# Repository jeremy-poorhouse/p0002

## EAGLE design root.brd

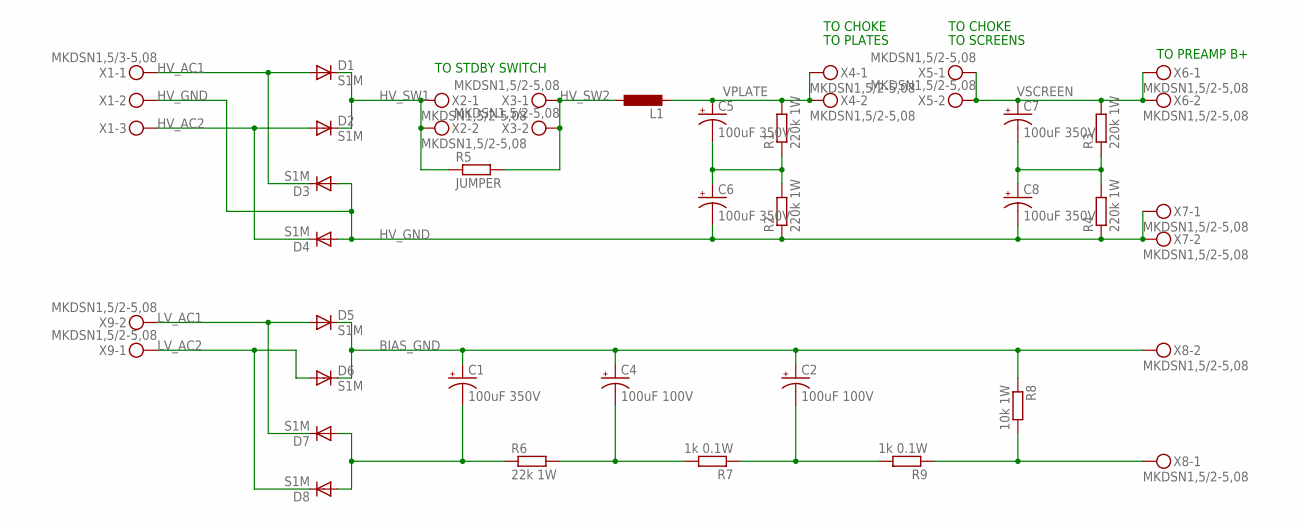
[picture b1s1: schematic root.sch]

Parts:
C1, C5, C6, C7, C8: 100uF 350V; E7,5-18
C2, C4: 100uF 100V; PANASONIC_F
D1, D2, D3, D4, D5, D6, D7, D8: S1M; SMA
L1: L-EUL4516C; L4516C
R1, R2, R3, R4: 220k 1W; R2512
R5: JUMPER; R1206
R6: 22k 1W; R2512
R7, R9: 1k 0.1W; R0603
R8: 10k 1W; R2512
X1: MKDSN1,5/3-5,08
X2, X3, X4, X5, X6, X7, X8, X9: MKDSN1,5/2-5,08

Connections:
BIAS_GND: C1.+, C2.+, C4.+, D5.C, D6.C, R8.1, X8.2
HV_AC1: D1.A, D3.C, X1.1
HV_AC2: D2.A, D4.C, X1.3
HV_GND: C6.-, C8.-, D3.A, D4.A, R2.1, R4.1, X1.2, X7.1, X7.2
HV_SW1: D1.C, D2.C, R5.1, X2.1, X2.2
HV_SW2: L1.1, R5.2, X3.1, X3.2
LV_AC1: D5.A, D7.C, X9.2
LV_AC2: D6.A, D8.C, X9.1
unnamed: C5.-, C6.+, R1.1, R2.2
unnamed: R8.2, R9.1, X8.1
unnamed: C4.-, R6.2, R7.2
unnamed: C7.-, C8.+, R3.1, R4.2
unnamed: C2.-, R7.1, R9.2
unnamed: C1.-, D7.A, D8.A, R6.1
VPLATE: C5.+, L1.2, R1.2, X4.1, X4.2
VSCREEN: C7.+, R3.2, X5.1, X5.2, X6.1, X6.2

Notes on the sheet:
TO STDBY SWITCH
TO PLATES
TO CHOKE
TO SCREENS
TO PREAMP B+

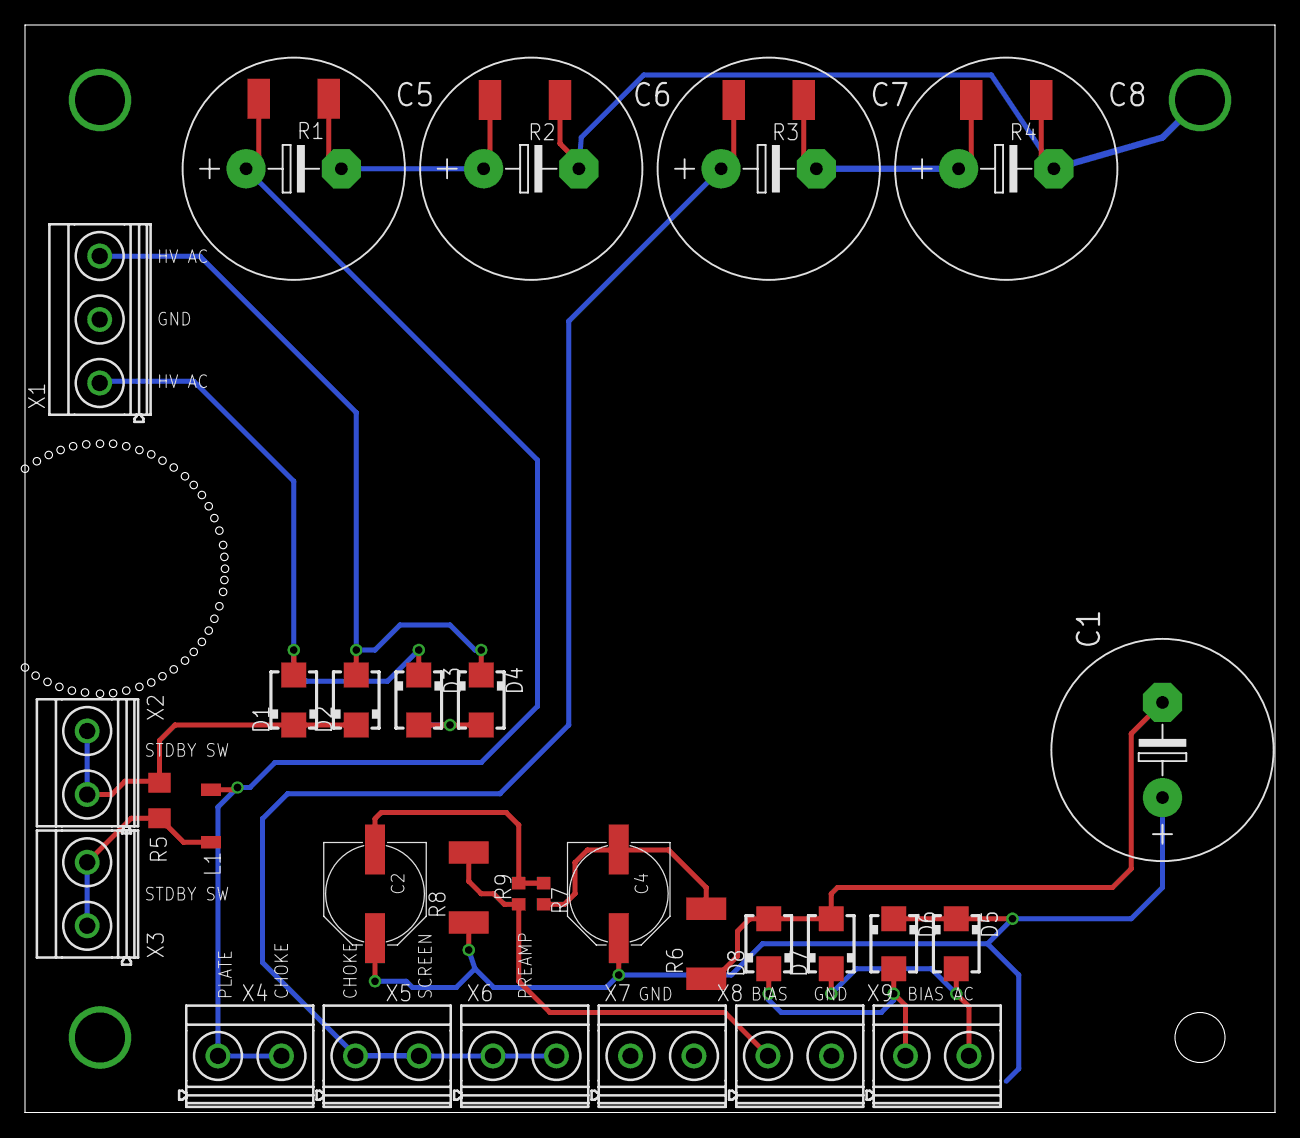
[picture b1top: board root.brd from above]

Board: 2 copper layers, 100.0 x 87.0 mm, 34 parts (0 on the bottom side), 16 nets.

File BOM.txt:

Partlist exported from /Users/jeremyhale/Documents/eagle/poorhouseamps/power_supply/root.sch at 2015-03-23 2:21 PM

Part Value           Device          Package         Description                          
C1   100uF 350V      CPOL-USE7.5-18  E7,5-18         POLARIZED CAPACITOR, American symbol 
C2   100uF 100V      CPOL-USF        PANASONIC_F     POLARIZED CAPACITOR, American symbol 
C4   100uF 100V      CPOL-USF        PANASONIC_F     POLARIZED CAPACITOR, American symbol 
C5   100uF 350V      CPOL-USE7.5-18  E7,5-18         POLARIZED CAPACITOR, American symbol 
C6   100uF 350V      CPOL-USE7.5-18  E7,5-18         POLARIZED CAPACITOR, American symbol 
C7   100uF 350V      CPOL-USE7.5-18  E7,5-18         POLARIZED CAPACITOR, American symbol 
C8   100uF 350V      CPOL-USE7.5-18  E7,5-18         POLARIZED CAPACITOR, American symbol 
D1   S1M             S1M             SMA                                                  
D2   S1M             S1M             SMA                                                  
D3   S1M             S1M             SMA                                                  
D4   S1M             S1M             SMA                                                  
D5   S1M             S1M             SMA                                                  
D6   S1M             S1M             SMA                                                  
D7   S1M             S1M             SMA                                                  
D8   S1M             S1M             SMA                                                  
L1                   L-EUL4516C      L4516C          INDUCTOR, European symbol            
R1   220k 1W         R-EU_R2512      R2512           RESISTOR, European symbol            
R2   220k 1W         R-EU_R2512      R2512           RESISTOR, European symbol            
R3   220k 1W         R-EU_R2512      R2512           RESISTOR, European symbol            
R4   220k 1W         R-EU_R2512      R2512           RESISTOR, European symbol            
R5   JUMPER          R-EU_R1206      R1206           RESISTOR, European symbol            
R6   22k 1W          R-EU_R2512      R2512           RESISTOR, European symbol            
R7   1k 1W           R-EU_R0603      R0603           RESISTOR, European symbol            
R8   10k 1W          R-EU_R2512      R2512           RESISTOR, European symbol            
R9   1k 1W           R-EU_R0603      R0603           RESISTOR, European symbol            
X1   MKDSN1,5/3-5,08 MKDSN1,5/3-5,08 MKDSN1,5/3-5,08 MKDSN 1,5/ 3-5,08 Printklemme        
X2   MKDSN1,5/2-5,08 MKDSN1,5/2-5,08 MKDSN1,5/2-5,08 MKDSN 1,5/ 2-5,08 Printklemme        
X3   MKDSN1,5/2-5,08 MKDSN1,5/2-5,08 MKDSN1,5/2-5,08 MKDSN 1,5/ 2-5,08 Printklemme        
X4   MKDSN1,5/2-5,08 MKDSN1,5/2-5,08 MKDSN1,5/2-5,08 MKDSN 1,5/ 2-5,08 Printklemme        
X5   MKDSN1,5/2-5,08 MKDSN1,5/2-5,08 MKDSN1,5/2-5,08 MKDSN 1,5/ 2-5,08 Printklemme        
X6   MKDSN1,5/2-5,08 MKDSN1,5/2-5,08 MKDSN1,5/2-5,08 MKDSN 1,5/ 2-5,08 Printklemme        
X7   MKDSN1,5/2-5,08 MKDSN1,5/2-5,08 MKDSN1,5/2-5,08 MKDSN 1,5/ 2-5,08 Printklemme        
X8   MKDSN1,5/2-5,08 MKDSN1,5/2-5,08 MKDSN1,5/2-5,08 MKDSN 1,5/ 2-5,08 Printklemme        
X9   MKDSN1,5/2-5,08 MKDSN1,5/2-5,08 MKDSN1,5/2-5,08 MKDSN 1,5/ 2-5,08 Printklemme

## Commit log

2015-03-23 generated output files
2015-03-31 released
